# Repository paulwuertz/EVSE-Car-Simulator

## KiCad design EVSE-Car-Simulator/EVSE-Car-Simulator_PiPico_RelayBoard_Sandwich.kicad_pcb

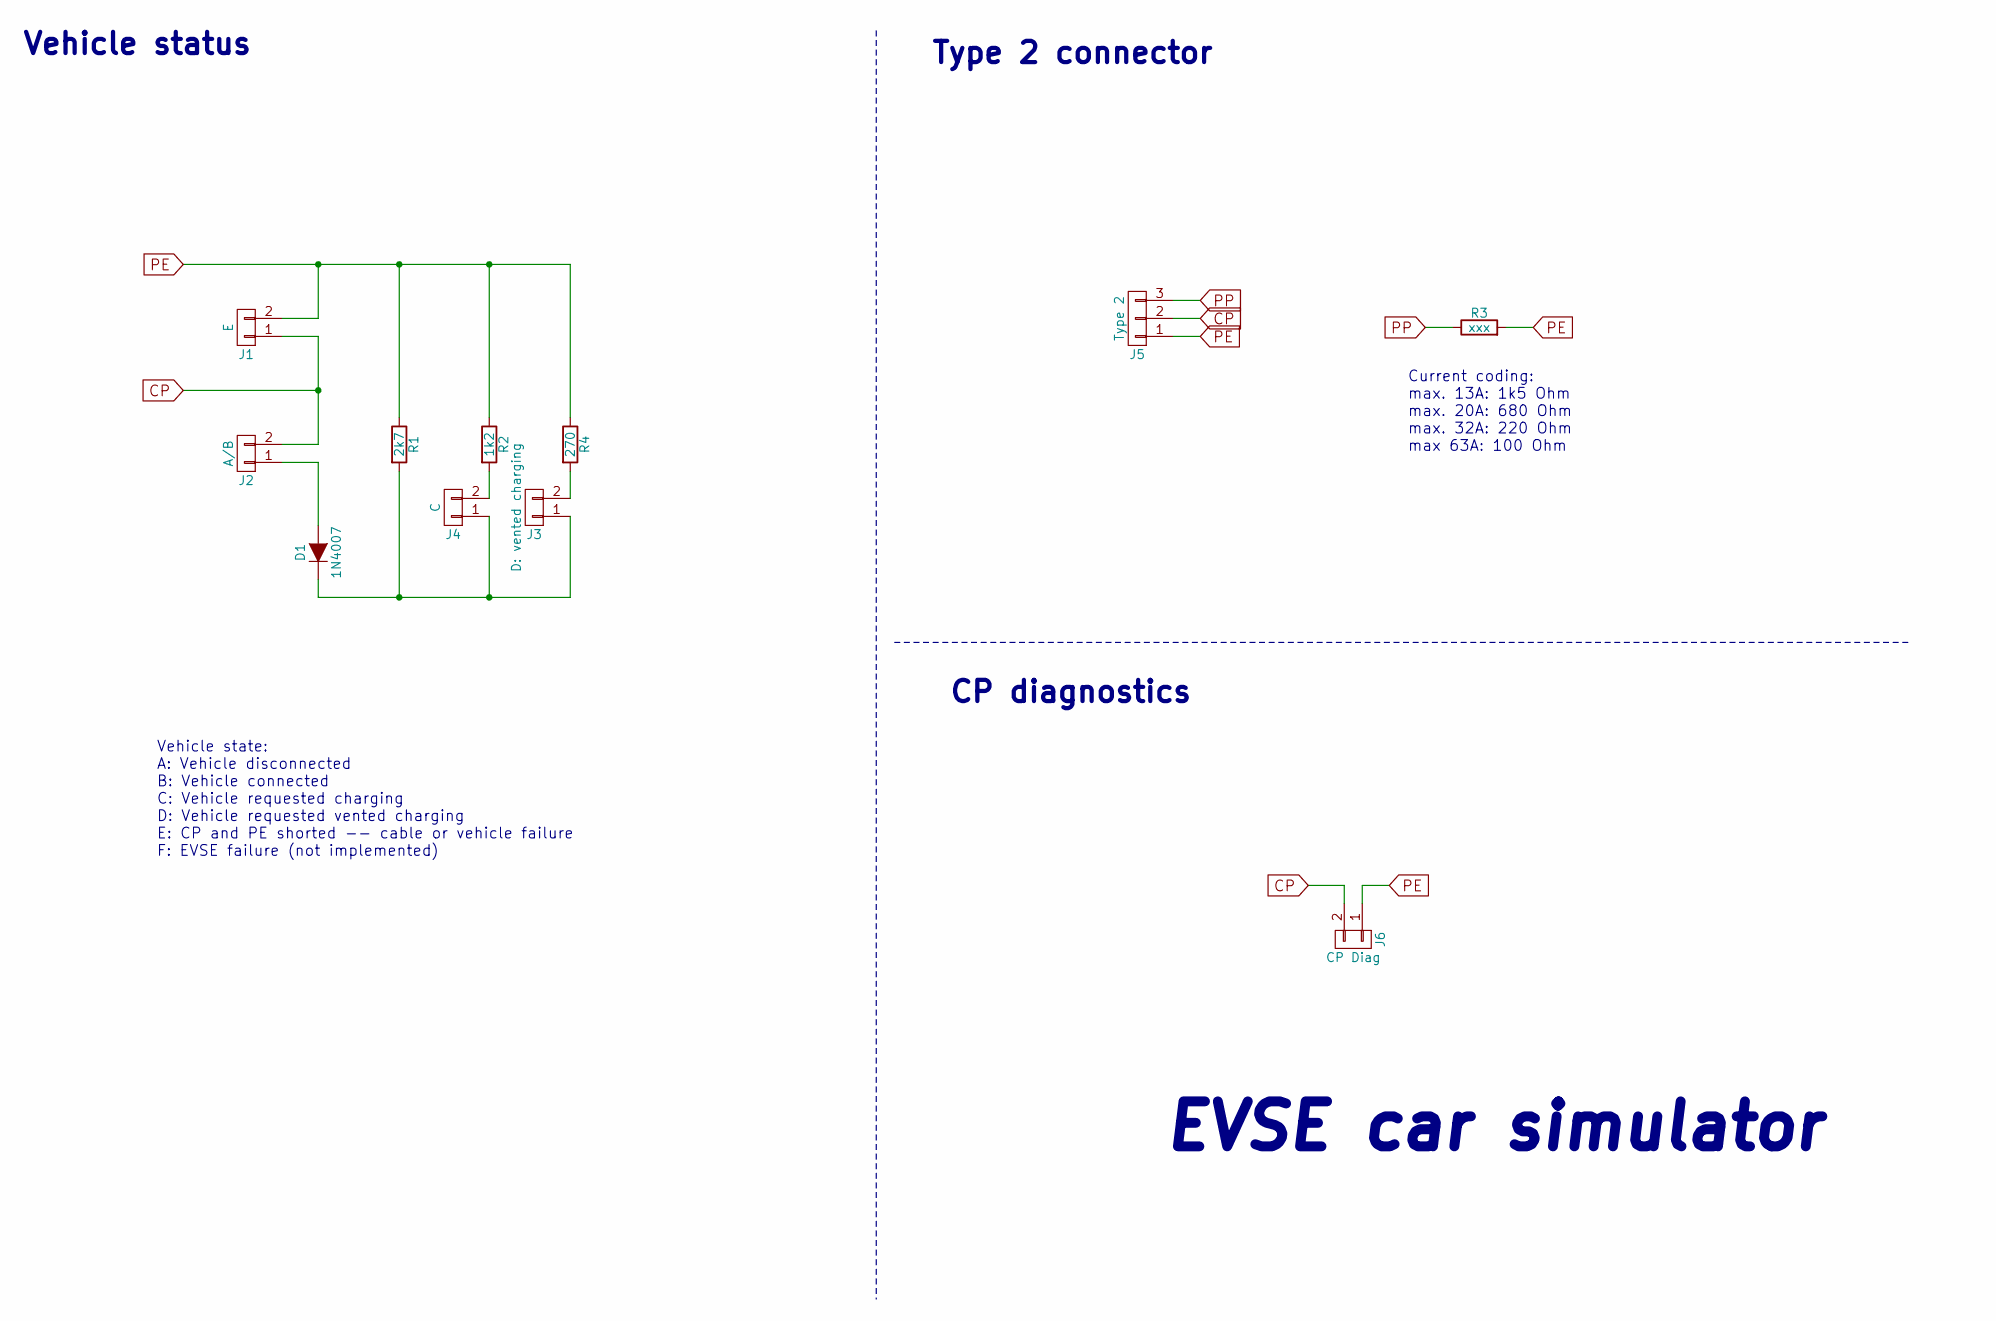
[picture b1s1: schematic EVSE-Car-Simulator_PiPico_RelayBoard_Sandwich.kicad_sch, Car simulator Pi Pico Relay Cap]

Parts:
D1: 1N4007; D_DO-41_SOD81_P7.62mm_Horizontal
J1: E; Type2-Solderpads_2hole
J2: A/B; Type2-Solderpads_2hole
J3: D: vented charging; Type2-Solderpads_2hole
J4: C; Type2-Solderpads_2hole
J5: Type 2; Type2-Solderpads
J6: CP Diag; PinHeader_1x02_P2.54mm_Vertical
R1: 2k7; R_Axial_DIN0204_L3.6mm_D1.6mm_P7.62mm_Horizontal
R2: 1k2; R_Axial_DIN0204_L3.6mm_D1.6mm_P7.62mm_Horizontal
R3: xxx; R_Axial_DIN0204_L3.6mm_D1.6mm_P7.62mm_Horizontal
R4: 270; R_Axial_DIN0204_L3.6mm_D1.6mm_P7.62mm_Horizontal

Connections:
CP: J1.1, J2.2, J5.2, J6.2
unnamed: D1.2 (A), J2.1
unnamed: D1.1 (K), J3.1, J4.1, R1.2
unnamed: J3.2, R4.2
unnamed: J4.2, R2.2
PE: J1.2, J5.1, J6.1, R1.1, R2.1, R3.2, R4.1
PP: J5.3, R3.1

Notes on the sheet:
Current coding: max. 13A: 1k5 Ohm max. 20A: 680 Ohm max. 32A: 220 Ohm max 63A: 100 Ohm
CP diagnostics
Vehicle state: A: Vehicle disconnected B: Vehicle connected C: Vehicle requested charging D: Vehicle requested vented charging E: CP and PE shorted -- cable or vehicle failure F: EVSE failure (not implemented)
Type 2 connector
EVSE car simulator
Vehicle status

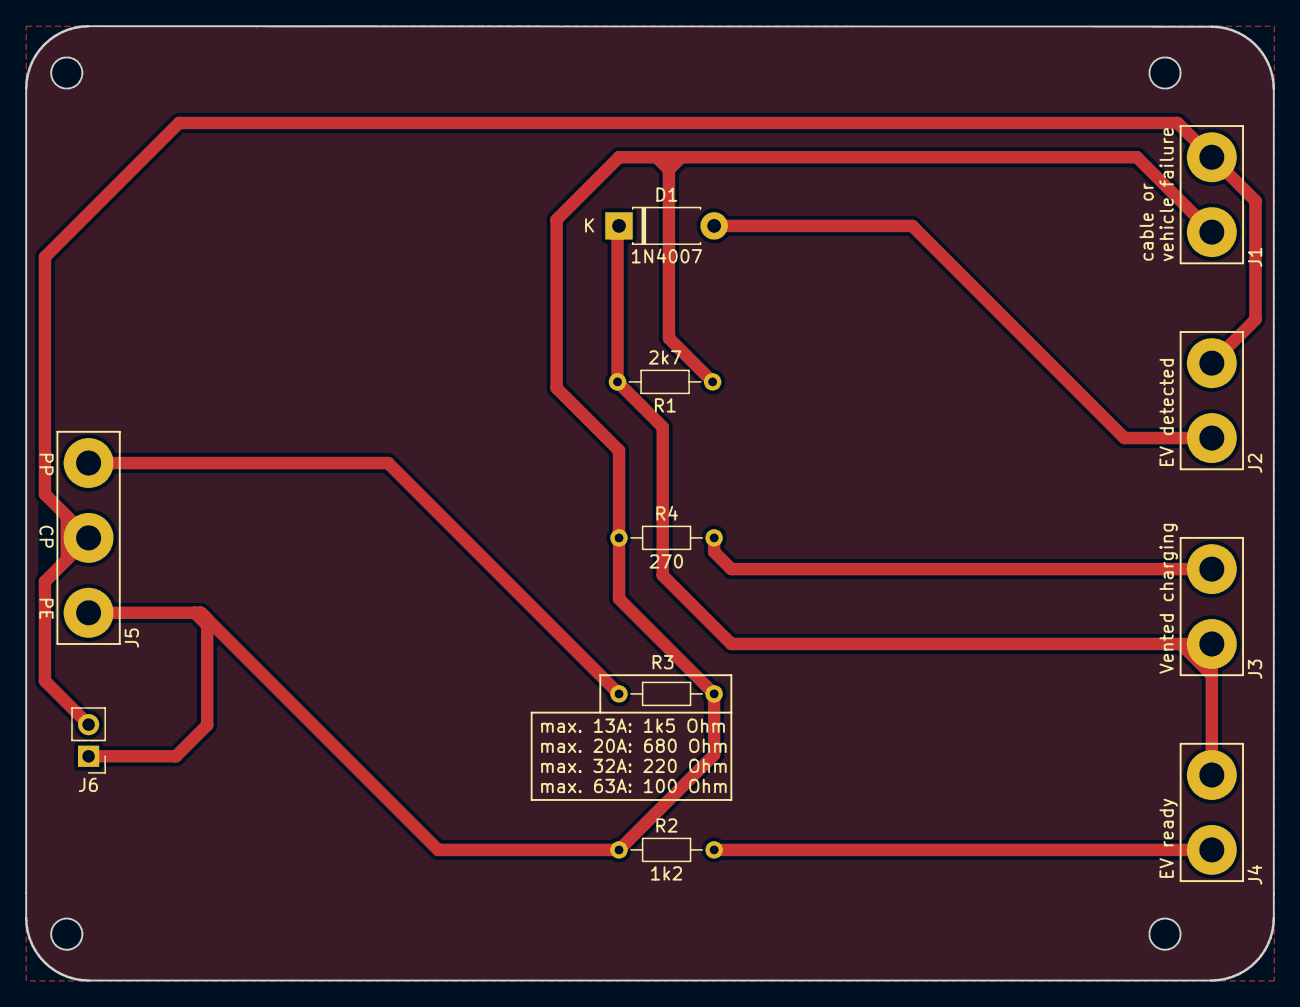
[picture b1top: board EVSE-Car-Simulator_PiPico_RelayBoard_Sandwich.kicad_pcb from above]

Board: 2 copper layers, 100.0 x 76.5 mm, 11 parts (0 on the bottom side), 7 nets.

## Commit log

2024-08-30 open files in kicad8
2024-08-31 add py pico relayboard project+sch+pcb
